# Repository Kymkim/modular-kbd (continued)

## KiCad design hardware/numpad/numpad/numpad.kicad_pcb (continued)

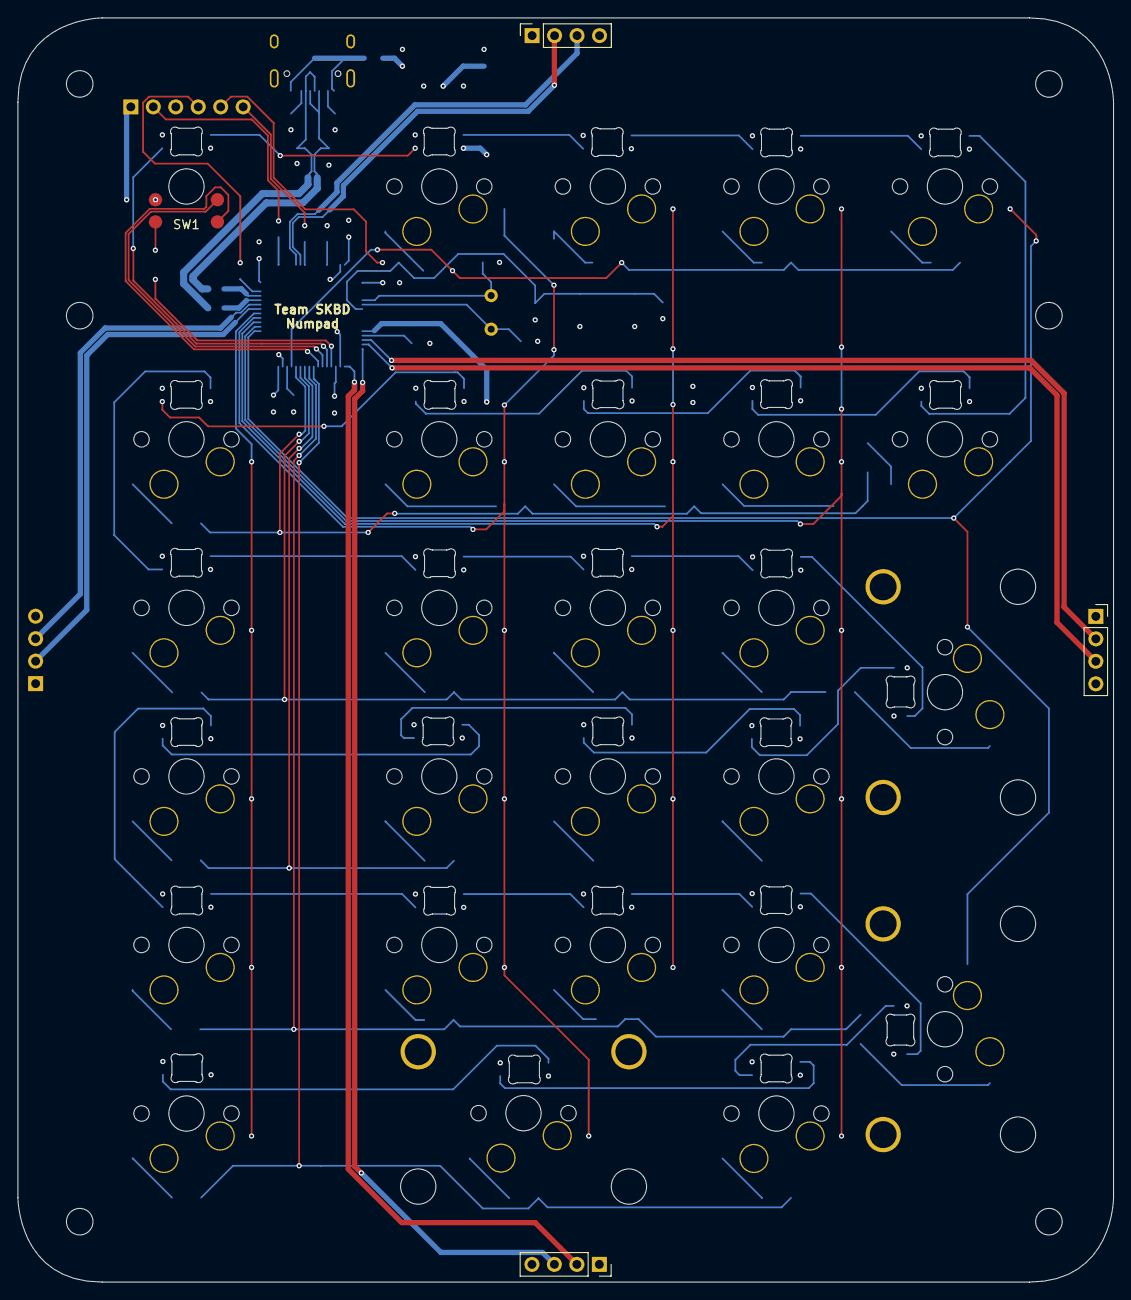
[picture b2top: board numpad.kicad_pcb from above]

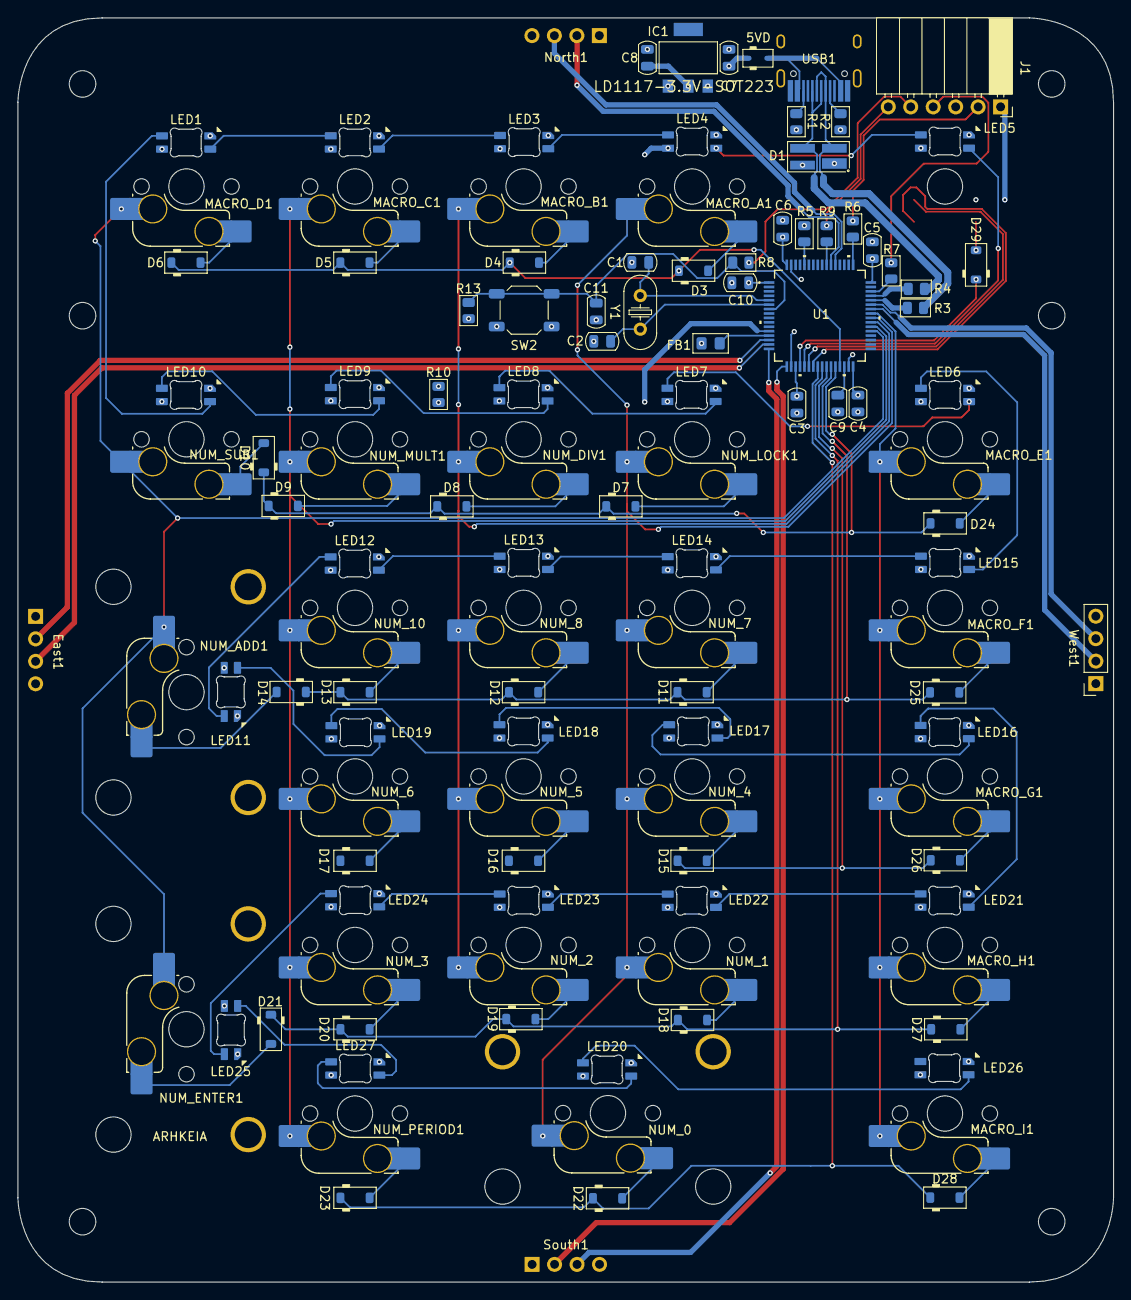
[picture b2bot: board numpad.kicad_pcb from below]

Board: 4 copper layers, 123.8 x 142.9 mm, 119 parts (112 on the bottom side), 100 nets.

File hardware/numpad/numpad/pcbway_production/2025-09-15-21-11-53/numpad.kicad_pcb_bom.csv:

Designator,Quantity,Value,Footprint,Package,MPN,DNP,Mount_Type,Description,Specifications,Manufacturer
"C1, C2",2,20pF,C_0805_2012Metric,,,,smt,"SMD 0805 MLCC capacitor, Alternate KiCad Library",,
"C10, C7",2,1uF,C_0805_2012Metric,,,,smt,"SMD 0805 MLCC capacitor, Alternate KiCad Library",,
C11,1,0.1uF,C_0805_2012Metric,,,,smt,"SMD 0805 MLCC capacitor, Alternate KiCad Library",,
"C3, C4, C5, C6",4,100nF,C_0805_2012Metric,,,,smt,"SMD 0805 MLCC capacitor, Alternate KiCad Library",,
C8,1,10uF,C_0805_2012Metric,,,,smt,"SMD 0805 MLCC capacitor, Alternate KiCad Library",,
C9,1,4.7uF,C_0805_2012Metric,,,,smt,"SMD 0805 MLCC capacitor, Alternate KiCad Library",,
D1,1,PRTR5V0U2X,SOT-143_Handsoldering,,,,smt,"SOT-143 TVS Diode Array, 2 protected lines, 5.5V, Alternate KiCAD Library",,
"D10, D11, D12, D13, D14, D15, D16, D17, D18, D19, D20, D21, D22, D23, D24, D25, D26, D27, D28, D29, D3, D4, D5, D6, D7, D8, D9",27,1N4148W,D_SOD-123,,,,smt,"SOD-123 Diode, Small Signal, Fast Switching, 75V, 150mA, 4ns, Alternate KiCad Library",,
D2,1,BAT60JFILM,D_SOD-323,,,,smt,Diode,,
"EAST, NORTH, SOUTH, WEST",4,Conn_01x04,PinSocket_1x04_P2.54mm_Vertical,,1-0401FBV0T,,tht,HEADER 1x4 MALE PINS 0.100” 180deg,HEADER 1x4 MALE PINS 0.100” 180deg,TAD
FB1,1,Ferrite_Bead,Fuse_0805_2012Metric_Pad1.15x1.40mm_BigPads,,,,smt,"Ferrite bead, Alternate KiCAD Library",,
IC1,1,LD1117,SOT223,,LD1117S33CTR,,tht,"3.3V Voltage Regulator, SOT-223-3, Imax=0.8A, VinMax=15V, Vdrop=1V",,STMicroelectronics
J1,1,Conn_01x06,PinSocket_1x06_P2.54mm_Horizontal,,1-0601FBV0T,,tht,HEADER 1x6 MALE PINS 0.100” 180deg,HEADER 1x6 MALE PINS 0.100” 180deg,TAD
"LED1, LED10, LED11, LED12, LED13, LED14, LED15, LED16, LED17, LED18, LED19, LED2, LED20, LED21, LED22, LED23, LED24, LED25, LED26, LED27, LED3, LED4, LED5, LED6, LED7, LED8, LED9",27,MX_SK6812MINI-E,LED_MX_6028R,,,,smt,Reverse mount adressable LED (WS2812 protocol),,
"MACRO_A1, MACRO_B1, MACRO_C1, MACRO_D1, MACRO_E1, MACRO_F1, MACRO_G1, MACRO_H1, MACRO_I1, NUM_0, NUM_1, NUM_10, NUM_2, NUM_3, NUM_4, NUM_5, NUM_6, NUM_7, NUM_8, NUM_ADD1, NUM_DIV1, NUM_ENTER1, NUM_LOCK1, NUM_MULT1, NUM_PERIOD1, NUM_SUB1",26,MX_SW_HS,SW_MX_HS_CPG151101S11_1u,,,,smt,"Push button switch, normally open, two pins, 45° tilted, Kailh CPG151101S11 for Cherry MX style switches",,
"R1, R2",2,5.1k,R_0805_2012Metric,,,,smt,"SMD 0805 Chip Resistor, European Symbol, Alternate KiCad Library",,
R10,1,DNP,R_0805_2012Metric,,,Yes,smt,"SMD 0805 Chip Resistor, European Symbol, Alternate KiCad Library",,
R13,1,DNP,R_0805_2012Metric,,,Yes,smt,"SMD 0805 Chip Resistor, European Symbol, Alternate KiCad Library",,
"R3, R4, R6, R7, R8, R9",6,22,R_0805_2012Metric,,,,smt,"SMD 0805 Chip Resistor, European Symbol, Alternate KiCad Library",,
R5,1,10k,R_0805_2012Metric,,,,smt,"SMD 0805 Chip Resistor, European Symbol, Alternate KiCad Library",,
"S1, S2, S3",3,MX_stab,STAB_MX_P_2u,,,,tht,Cherry MX-style stabilizer,,
SW2,1,Push_Button,SW_SPST_SKQG_WithStem,,,,smt,Common 6mmx6mm Push Button,,
U1,1,~,LQFP64-10x10mm,,,,smt,,,
USB1,1,HRO-TYPE-C-31-M-12,HRO-TYPE-C-31-M-12-HandSoldering,,,,smt,,,
Y1,1,8MHz,Crystal_HC52-U_Vertical,,,,tht,8Mz Crystal,,

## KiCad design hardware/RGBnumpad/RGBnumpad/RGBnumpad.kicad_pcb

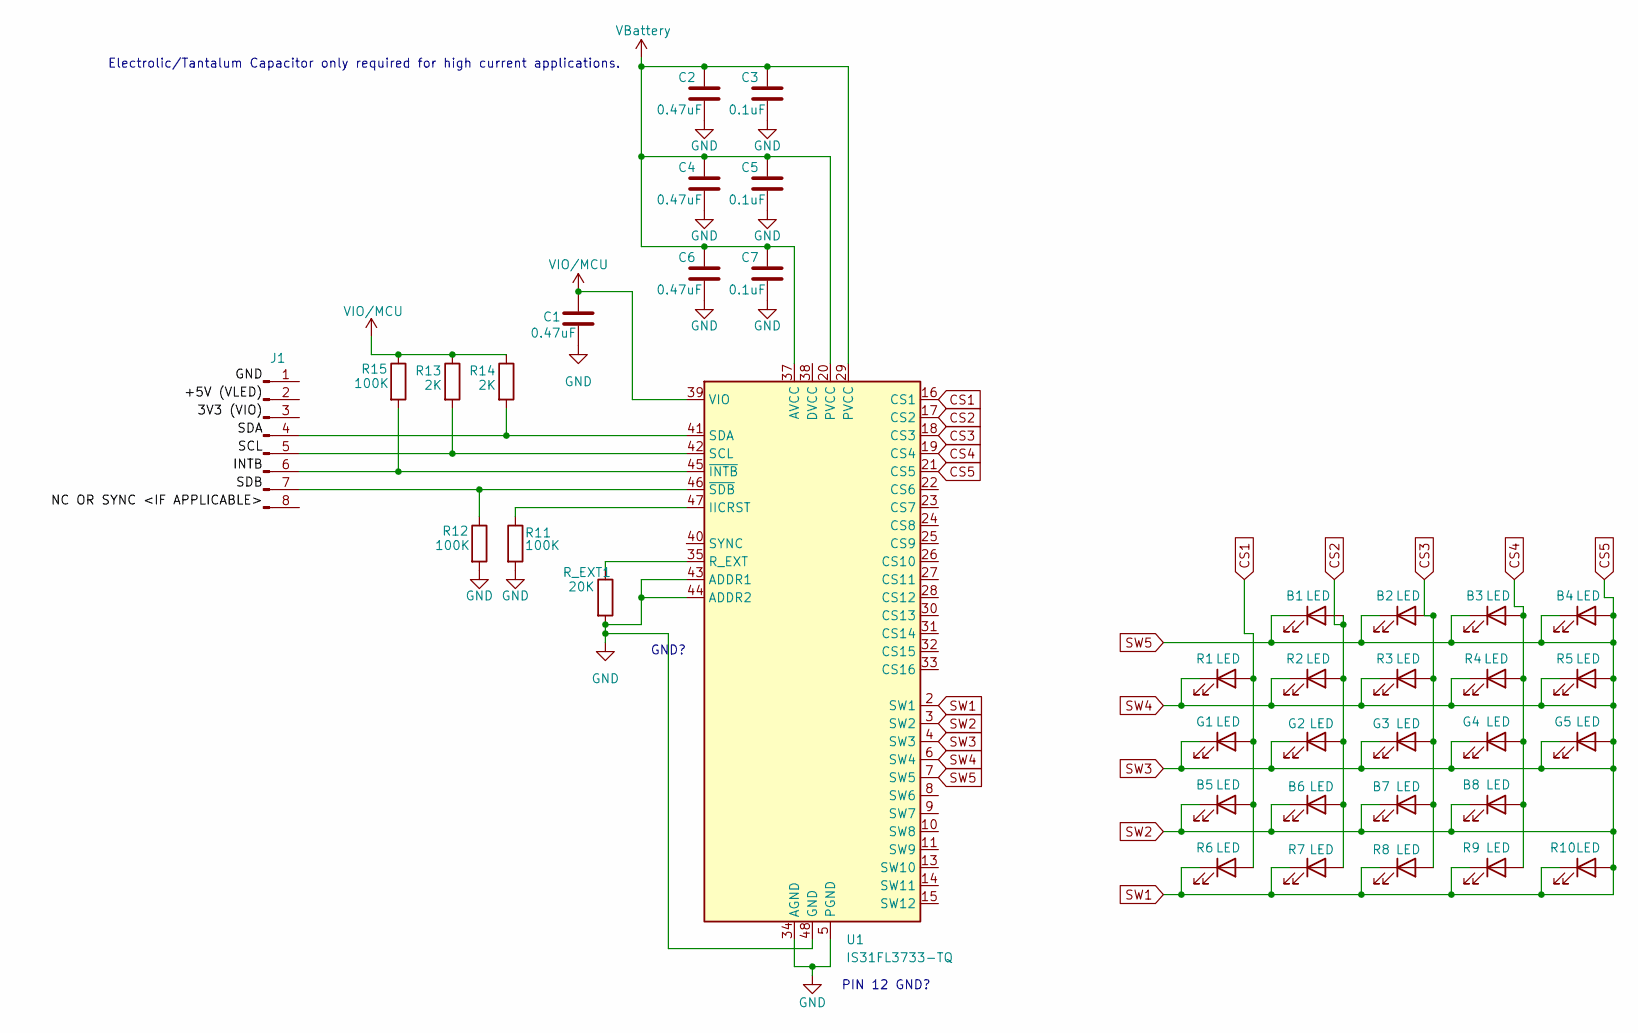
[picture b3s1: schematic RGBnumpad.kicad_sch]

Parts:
B1, B2, B3, B4, B5, B6, B7, B8: LED; LED_0805_2012Metric_Pad1.15x1.40mm_HandSolder
C1, C2, C4, C6: 0.47uF; C_0805_2012Metric_Pad1.18x1.45mm_HandSolder
C3, C5, C7: 0.1uF; C_0805_2012Metric_Pad1.18x1.45mm_HandSolder
G1, G2, G3, G4, G5: LED; LED_0805_2012Metric_Pad1.15x1.40mm_HandSolder
J1: (no value)
R1, R2, R3, R4, R5, R6, R7, R8, R9, R10: LED; LED_0805_2012Metric_Pad1.15x1.40mm_HandSolder
R11, R12, R15: 100K; R_0805_2012Metric_Pad1.20x1.40mm_HandSolder
R13, R14: 2K; R_0805_2012Metric_Pad1.20x1.40mm_HandSolder
R_EXT1: 20K; R_0805_2012Metric_Pad1.20x1.40mm_HandSolder
U1: IS31FL3733-TQ; TQFP-48-1EP_7x7mm_P0.5mm_EP5x5mm

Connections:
CS1: B5.2 (A), G1.2 (A), R1.2 (A), R6.2 (A), U1.16 (CS1)
CS2: B1.2 (A), B6.2 (A), G2.2 (A), R2.2 (A), R7.2 (A), U1.17 (CS2)
CS3: B2.2 (A), B7.2 (A), G3.2 (A), R3.2 (A), R8.2 (A), U1.18 (CS3)
CS4: B3.2 (A), B8.2 (A), G4.2 (A), R4.2 (A), R9.2 (A), U1.19 (CS4)
CS5: B1.1 (K), B2.1 (K), B3.1 (K), B4.1 (K), B4.2 (A), B5.1 (K), B6.1 (K), B7.1 (K), B8.1 (K), G1.1 (K), G2.1 (K), G3.1 (K), G4.1 (K), G5.1 (K), G5.2 (A), R1.1 (K), R2.1 (K), R3.1 (K), R4.1 (K), R5.1 (K), R5.2 (A), R6.1 (K), R7.1 (K), R8.1 (K), R9.1 (K), R10.1 (K), R10.2 (A), U1.2 (SW1), U1.3 (SW2), U1.4 (SW3), U1.6 (SW4), U1.7 (SW5), U1.21 (CS5)
GND: C1.2, C2.2, C3.2, C4.2, C5.2, C6.2, C7.2, R11.2, R12.2, R_EXT1.2, U1.5 (PGND), U1.12 (PGND), U1.34 (AGND), U1.43 (ADDR1), U1.44 (ADDR2), U1.48 (GND), U1.49 (GND)
unnamed: J1.4, R14.2, U1.41 (SDA)
unnamed: J1.5, R13.2, U1.42 (SCL)
unnamed: J1.6, R15.2, U1.45 (~INTB)
unnamed: J1.7, R12.1, U1.46 (~SDB)
unnamed: R11.1, U1.47 (IICRST)
unnamed: R_EXT1.1, U1.35 (R_EXT)
VBattery: C2.1, C3.1, C4.1, C5.1, C6.1, C7.1, U1.20 (PVCC), U1.29 (PVCC), U1.37 (AVCC)
VIO/MCU: C1.1, R13.1, R14.1, R15.1, U1.39 (VIO)

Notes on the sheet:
PIN 12 GND?
Electrolic/Tantalum Capacitor only required for high current applications.
GND?

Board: 2 copper layers, 37 parts (0 on the bottom side), 14 nets, no tracks yet.

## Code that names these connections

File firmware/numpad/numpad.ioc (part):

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Mcu.Name=STM32F446R(C-E)Tx
Mcu.Package=LQFP64
Mcu.UserName=STM32F446RETx
PA0-WKUP.Mode=Asynchronous
PA0-WKUP.Signal=UART4_TX
PA1.Mode=Asynchronous
PA1.Signal=UART4_RX
PA10.Mode=Asynchronous
PA10.Signal=USART1_RX
PA11.Mode=Device_Only
PA11.Signal=USB_OTG_FS_DM
PA12.Mode=Device_Only
PA12.Signal=USB_OTG_FS_DP
PA13.Mode=Serial_Wire
PA13.Signal=SYS_JTMS-SWDIO
PA14.Mode=Serial_Wire
PA14.Signal=SYS_JTCK-SWCLK
PA2.Mode=Asynchronous
PA2.Signal=USART2_TX
PA3.Mode=Asynchronous
PA3.Signal=USART2_RX
PA8.GPIOParameters=GPIO_Label
PA8.GPIO_Label=COL4
PA8.Signal=GPIO_Output
PA9.Mode=Asynchronous
PA9.Signal=USART1_TX
PB0.GPIOParameters=GPIO_PuPd,GPIO_Label
PB0.GPIO_Label=ROW4
PB0.GPIO_PuPd=GPIO_PULLDOWN
PB0.Signal=GPIO_Input
PB1.GPIOParameters=GPIO_PuPd,GPIO_Label
PB1.GPIO_Label=ROW3
PB1.GPIO_PuPd=GPIO_PULLDOWN
PB1.Signal=GPIO_Input
PB10.GPIOParameters=GPIO_PuPd,GPIO_Label
PB10.GPIO_Label=ROW1SR
PB10.GPIO_PuPd=GPIO_PULLDOWN
PB10.Signal=GPIO_Input
PB2.GPIOParameters=GPIO_PuPd,GPIO_Label
PB2.GPIO_Label=ROW2
PB2.GPIO_PuPd=GPIO_PULLDOWN
PB2.Signal=GPIO_Input
PB4.GPIOParameters=GPIO_Label
PB4.GPIO_Label=WDebug
PB4.Signal=GPIO_Output
PB5.GPIOParameters=GPIO_Label
PB5.GPIO_Label=SDebug
PB5.Signal=GPIO_Output
PB6.GPIOParameters=GPIO_Label
PB6.GPIO_Label=EDebug
PB6.Signal=GPIO_Output
PB7.GPIOParameters=GPIO_Label
PB7.GPIO_Label=NDebug
PB7.Signal=GPIO_Output
PB8.Mode=I2C
PB8.Signal=I2C1_SCL
PB9.Mode=I2C
PB9.Signal=I2C1_SDA
PC12.Mode=Asynchronous
PC12.Signal=UART5_TX
PC4.GPIOParameters=GPIO_PuPd,GPIO_Label
PC4.GPIO_Label=ROW6
PC4.GPIO_PuPd=GPIO_PULLDOWN
PC4.Signal=GPIO_Input
PC5.GPIOParameters=GPIO_PuPd,GPIO_Label
PC5.GPIO_Label=ROW5
PC5.GPIO_PuPd=GPIO_PULLDOWN
PC5.Signal=GPIO_Input
PC7.GPIOParameters=GPIO_Label
PC7.GPIO_Label=COL1
PC7.Signal=GPIO_Output
PC8.GPIOParameters=GPIO_Label
PC8.GPIO_Label=COL2
PC8.Signal=GPIO_Output
PC9.GPIOParameters=GPIO_Label
PC9.GPIO_Label=COL3
PC9.Signal=GPIO_Output
PD2.Mode=Asynchronous
PD2.Signal=UART5_RX
PH0-OSC_IN.Mode=HSE-External-Oscillator
PH0-OSC_IN.Signal=RCC_OSC_IN
PH1-OSC_OUT.Mode=HSE-External-Oscillator
PH1-OSC_OUT.Signal=RCC_OSC_OUT
board=custom

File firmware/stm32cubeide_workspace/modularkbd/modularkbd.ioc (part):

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Mcu.Name=STM32F446R(C-E)Tx
Mcu.Package=LQFP64
Mcu.UserName=STM32F446RETx
PA0-WKUP.Mode=Asynchronous
PA0-WKUP.Signal=UART4_TX
PA1.Mode=Asynchronous
PA1.Signal=UART4_RX
PA10.Mode=Asynchronous
PA10.Signal=USART1_RX
PA11.Mode=Device_Only
PA11.Signal=USB_OTG_FS_DM
PA12.Mode=Device_Only
PA12.Signal=USB_OTG_FS_DP
PA13.Mode=JTAG_5_pins
PA13.Signal=SYS_JTMS-SWDIO
PA14.Mode=JTAG_5_pins
PA14.Signal=SYS_JTCK-SWCLK
PA15.Mode=JTAG_5_pins
PA15.Signal=SYS_JTDI
PA2.Mode=Asynchronous
PA2.Signal=USART2_TX
PA3.Mode=Asynchronous
PA3.Signal=USART2_RX
PA5.Signal=S_TIM2_CH1_ETR
PA6.Signal=S_TIM3_CH1
PA7.Signal=S_TIM3_CH2
PA8.Signal=GPIO_Output
PA9.Mode=Asynchronous
PA9.Signal=USART1_TX
PB0.Signal=GPIO_Input
PB1.Signal=GPIO_Input
PB10.Signal=GPIO_Input
PB2.Signal=GPIO_Input
PB3.Mode=JTAG_5_pins
PB3.Signal=SYS_JTDO-SWO
PB4.Mode=JTAG_5_pins
PB4.Signal=SYS_JTRST
PB6.Mode=I2C
PB6.Signal=I2C1_SCL
PB7.Mode=I2C
PB7.Signal=I2C1_SDA
PC10.Mode=Asynchronous
PC10.Signal=USART3_TX
PC11.Mode=Asynchronous
PC11.Signal=USART3_RX
PC12.Mode=Asynchronous
PC12.Signal=UART5_TX
PC4.Signal=GPIO_Input
PC5.Signal=GPIO_Input
PC6.Signal=GPIO_Output
PC7.Signal=GPIO_Output
PC8.Signal=GPIO_Output
PC9.Signal=GPIO_Output
PD2.Mode=Asynchronous
PD2.Signal=UART5_RX
PH0-OSC_IN.Mode=HSE-External-Oscillator
PH0-OSC_IN.Signal=RCC_OSC_IN
PH1-OSC_OUT.Mode=HSE-External-Oscillator
PH1-OSC_OUT.Signal=RCC_OSC_OUT
RCC.HSE_VALUE=8000000
board=custom

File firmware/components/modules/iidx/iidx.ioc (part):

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Mcu.Name=STM32F446R(C-E)Tx
Mcu.Package=LQFP64
Mcu.UserName=STM32F446RETx
PA0-WKUP.GPIOParameters=GPIO_Label
PA0-WKUP.GPIO_Label=SCRATCH A
PA0-WKUP.Signal=S_TIM2_CH1_ETR
PA1.GPIOParameters=GPIO_Label
PA1.GPIO_Label=SCRATCH B
PA1.Signal=S_TIM2_CH2
PA10.GPIOParameters=GPIO_Label
PA10.GPIO_Label=COL 1
PA10.Signal=GPIO_Output
PA11.Mode=Device_Only
PA11.Signal=USB_OTG_FS_DM
PA12.Mode=Device_Only
PA12.Signal=USB_OTG_FS_DP
PA13.GPIOParameters=GPIO_Label
PA13.GPIO_Label=TMS
PA13.Mode=Serial_Wire
PA13.Signal=SYS_JTMS-SWDIO
PA14.GPIOParameters=GPIO_Label
PA14.GPIO_Label=TCK
PA14.Mode=Serial_Wire
PA14.Signal=SYS_JTCK-SWCLK
PA2.GPIOParameters=GPIO_Label
PA2.GPIO_Label=USART_TX
PA2.Mode=Asynchronous
PA2.Signal=USART2_TX
PA3.GPIOParameters=GPIO_Label
PA3.GPIO_Label=USART_RX
PA3.Mode=Asynchronous
PA3.Signal=USART2_RX
PA5.GPIOParameters=GPIO_Label
PA5.GPIO_Label=LD2 [Green Led]
PA5.Signal=GPIO_Output
PA6.GPIOParameters=GPIO_Label
PA6.GPIO_Label=LEFT LASER A
PA6.Signal=S_TIM3_CH1
PA7.GPIOParameters=GPIO_Label
PA7.GPIO_Label=LEFT LASER B
PA7.Signal=S_TIM3_CH2
PA8.GPIOParameters=GPIO_Label
PA8.GPIO_Label=COL 3
PA8.Signal=GPIO_Output
PA9.GPIOParameters=GPIO_Label
PA9.GPIO_Label=COL 2
PA9.Signal=GPIO_Output
PB12.GPIOParameters=GPIO_Label
PB12.GPIO_Label=EFFECT
PB12.Signal=GPIO_Input
PB13.GPIOParameters=GPIO_Label
PB13.GPIO_Label=VEFX
PB13.Signal=GPIO_Input
PB14.GPIOParameters=GPIO_PuPd,GPIO_Label
PB14.GPIO_Label=SEL
PB14.GPIO_PuPd=GPIO_PULLDOWN
PB14.Signal=GPIO_Input
PB15.GPIOParameters=GPIO_PuPd,GPIO_Label
PB15.GPIO_Label=START
PB15.GPIO_PuPd=GPIO_PULLDOWN
PB15.Signal=GPIO_Input
PB6.GPIOParameters=GPIO_Label
PB6.GPIO_Label=RIGHT LASER B
PB6.Signal=S_TIM4_CH1
PB7.GPIOParameters=GPIO_Label
PB7.GPIO_Label=RIGHT LASER A
PB7.Signal=S_TIM4_CH2
PB8.Mode=CAN_Activate
PB8.Signal=CAN1_RX
PB9.Mode=CAN_Activate
PB9.Signal=CAN1_TX
PC13.GPIOParameters=GPIO_Label,GPIO_ModeDefaultEXTI
PC13.GPIO_Label=B1 [Blue PushButton]
PC13.GPIO_ModeDefaultEXTI=GPIO_MODE_IT_FALLING
PC13.Signal=GPXTI13
PC14-OSC32_IN.Mode=LSE-External-Oscillator
PC14-OSC32_IN.Signal=RCC_OSC32_IN
PC15-OSC32_OUT.Mode=LSE-External-Oscillator
PC15-OSC32_OUT.Signal=RCC_OSC32_OUT
PC6.GPIOParameters=GPIO_PuPd,GPIO_Label
PC6.GPIO_Label=KEY 1
PC6.GPIO_PuPd=GPIO_PULLDOWN
PC6.Signal=GPXTI6
PC7.GPIOParameters=GPIO_Label
PC7.GPIO_Label=ROW 3
PC7.Signal=GPIO_Input
PC8.GPIOParameters=GPIO_Label
PC8.GPIO_Label=ROW 2
PC8.Signal=GPIO_Input
PC9.GPIOParameters=GPIO_Label
PC9.GPIO_Label=ROW 1
PC9.Signal=GPIO_Input
PH0-OSC_IN.Mode=HSE-External-Oscillator
PH0-OSC_IN.Signal=RCC_OSC_IN
PH1-OSC_OUT.Mode=HSE-External-Oscillator
PH1-OSC_OUT.Signal=RCC_OSC_OUT
RCC.HSE_VALUE=8000000
RCC.SYSCLKFreq_VALUE=72000000
RCC.SYSCLKSource=RCC_SYSCLKSOURCE_PLLCLK
board=NUCLEO-F446RE
boardIOC=true

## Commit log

2025-03-08 initial commit (i think)
2025-03-19 mainboard stuff
2025-03-21 updated code (untested)
2025-03-24 config update
2025-03-24 started on test module
2025-03-24 test module stuff
2025-06-06 config for the can bus for module
2025-06-07 CAN main start
2025-06-10 add git branch for can
2025-06-11 file restructuring and minor code edits with config
2025-06-11 deleted unused files
2025-06-13 update USB product string and include paths for CAN module. starting code with CAN as loopback to check if its working. not yet tested
2025-06-19 peepee
2025-06-19 Add working 2x2 matrix keypad main.c
2025-06-19 Add full STM32CubeIDE SKBD_Matrix project for 2x2 keypad
2025-06-20 Add USB device descriptor and configuration for KMDVX Controller
    - Implemented USB device descriptors in usbd_desc.c for HID functionality.
    - Created iidx.ioc file for STM32CubeMX configuration, defining peripherals and settings.
    - Added platformio.ini for PlatformIO project configuration targeting Nucleo-F446RE.
    - Introduced stm32pio.ini for integration with STM32CubeMX and PlatformIO commands.
2025-06-22 minor code change
2025-06-22 not working. should make the led flash if button on pa10 is pressed.
2025-06-24 Note on STM32 CAN Filter Bank Number
2025-06-25 working transmit data
2025-06-25 fix: update CAN filter bank configuration to valid range
2025-06-25 can finally works
2025-06-25 Add CAN communication and GPIO control functionality
    - Created HAL configuration file for STM32F1xx (stm32f1xx_hal_conf.h).
    - Added interrupt handler definitions in stm32f1xx_it.h.
    - Implemented CAN initialization and configuration in can.c.
    - Configured GPIO pins for output and external interrupts in gpio.c.
    - Developed main application logic in main.c for toggling an LED and sending CAN messages.
    - Implemented MSP initialization and de-initialization for CAN in stm32f1xx_hal_msp.c.
2025-06-25 Initial folder structure. added read me. will explain more details later
2025-06-26 some readme changes
2025-06-26 explaination for the mainboard stuff
2025-06-26 initial main board
2025-07-01 nkro support :)
2025-07-01 4key miku keyboard with nkro
2025-07-02 initial stuff for recieving from can
2025-07-02 separated usb code to the library. will add 6key rollover support later :)
2025-07-03 6 Key Rollover Code Comments
    check the addHIDReport function and the main function, memset line, verify
2025-07-03 separated HID struct for both nkro and 6kro
2025-07-12 Initial branch for can tester for the mainboard
2025-07-15 sample 2x2 modul
2025-07-15 folder re-structuring
2025-07-15 file restructure
2025-07-15 prototype mainboard done!
2025-07-22 dynamic mode implementation
2025-08-18 mergy
2025-08-18 Licensce and file restructuring. Housekeeping rules
2025-08-18 update read me
2025-08-18 connectors for other modules
2025-08-18 Numpad IOC
2025-08-19 Create LICENSE
2025-08-20 numpad ioc update for future compability with sync uart
2025-08-20 initial code for numpadtesting with UART
2025-08-22 DMA Queue implemntation using UART
2025-08-24 revised DMA Queue
2025-08-25 documentation and inactive mode code
2025-08-25 fixed compiler errors
2025-08-25 added todo tasks
2025-08-25 typo fix
2025-08-25 tpyo fix
2025-08-25 USB; Coupling Caps; and XTAL schematic
2025-08-26 Some work on the GPIO, enabled DMA for TX as well
2025-08-26 numpad, connections, and more
2025-08-27 progreers
2025-08-27 stuff
2025-08-27 draft pcb
2025-08-28 typo in schematic
    i changed the GNDA to AGND
2025-08-28 diode name + agnd --> gnd
    added the bat and added the jump from agnd and gnd that mayyyyy be needed
2025-09-01 RGBnumpad
    Added RBGnumpad w/ symbols
    Still need to assign footprints
2025-09-02 RGBnumpad Footprint
    SMD 0805 hand solder footprints assigned to all of the parts on schematic
2025-09-02 ICANTDOTHISRGBPCB
    ICANTDOITICANTDOITICANTDOITICANTDOITICANTDOITICANTDOITICANTDOITICANTDOITICANTDOITICANTDOITICANTDOITICANTDOITICANTDOITICANTDOITICANTDOITICANTDOITICANTDOITICANTDOITICANTDOITICANTDOIT
2025-09-02 some config changes
2025-09-03 rgb matrix and drc rules
2025-09-03 comments
2025-09-03 fixed grid
    19.05 is grid size for pcb editor
2025-09-04 backup
2025-09-04 ROT_SW
    Disconnect after S diode, ROT_SW
2025-09-04 LEDs attached to switches
    LEDs are assigned to the switches now
2025-09-05 some fixy
2025-09-05 sotfware fore re-enum and clock stabilize delay
2025-09-07 6kro rollback
2025-09-07 remaking a new firmware
2025-09-07 working 6kro
2025-09-08 archived old files
2025-09-08 Update Main for 2x2 HID keyboard
    Updated the main.c file to implement a 2x2 matrix keyboard functionality. The code now reads key presses and sends corresponding HID reports.
2025-09-09 pcb stuff
2025-09-09 diodes placed except top 2 rows
    🐷
2025-09-09 LEDs
    Placed all LEDs
2025-09-10 pcb design draft
2025-09-11 bom list and some minor changes
2025-09-11 messages
2025-09-14 commit before merging to dev
2025-09-14 docs change
2025-09-14 readmeupdate
2025-09-16 really necessary silkscreen on pcb numpad
2025-09-17 removed a file
2025-09-17 amogus sussy burger
2025-09-21 idk actually
2025-09-22 UART STUFF
2025-09-22 initial 65 perc
2025-09-23 keyboardMatrix
    finished the kbd matrix layout. subject to review. <3
2025-09-23 uart dma stuff
2025-09-23 numpad configuration
2025-09-23 removed buggy file
2025-09-24 PCB start for keyboard
2025-09-24 more pcb work
2025-09-24 keyboard updates
2025-09-24 chicken butt
2025-09-24 keyboard
2025-09-25 dma sending stuff thru uart
2025-09-25 stuff stabs O
2025-09-25 switches
2025-09-27 layout adjustment
2025-09-29 handshake event implementation
2025-09-29 somebody once told me the world is gonna roll me
2025-10-07 LEDs
2025-10-07 prototypeNumpadCase
    not done yet. only bottom done need extrude cuts on the top for mx holes
2025-10-13 completed protype numpad case
    fuck my chungus life
2025-10-13 stl files for numpad
    to da 3-d printer
2025-10-22 safty
2025-10-24 footprint
2025-10-28 diode placement
2025-10-29 pushy
2025-10-31 traces
2025-11-04 Traces
    67676767676767
    SIX SEVEN
2025-11-05 traces
    676767676767
2025-11-05 traces
    six seven
2025-11-07 autoroute
2025-11-08 fixed grouped words
    madafakers
2025-11-09 pcb update
2025-11-11 quotes
2025-11-11 minor stuff
2025-11-11 67 prototype
2025-11-12 somewhat works
2025-11-12 clean up
2025-11-12 ntearsntei
2025-11-17 googoogaagaa babies
2025-11-19 Implement encoder processing for keypress updates
    Added encoder processing to handle rotary input and update keypress reports accordingly.
2025-11-19 top mxPlate half
    not done yet but the top thing is done without the back part
2025-11-20 fnished top plate
    heeheehawhaw
2025-11-20 PhoPlate/Secure
    plate and supporting beams based on nolan keeb design
2025-11-21 left side PhoBottomCase complete
    i finished the left side of the bottom of the case. may need more joint in middle and need screw holes
2025-11-22 PhoBottomRight Case + Assembly
    Both have been completed. awaiting m3 holes and top plate.
2025-11-22 assets
2025-11-22 reorg
2025-11-23 fixed alignment with wireframe
    need top alignment with screws and etch and rubber feet
2025-11-24 COMPLETED CASE
    pending engrave and writing
2025-11-25 print bottom
    hehehehaw
2025-11-26 67 partial code
2025-11-26 Updated key matrix
2025-11-27 complete Numpad Case
    gasket mounted goodness
2025-12-02 FINISHED FUCKING CASES
    RAHHHHHHHHHHHHHHHHH
2025-12-03 SQUIRT
2025-12-08 Refactor main.c for improved functionality and structure
    Updated the main.c file to include additional functionalities and improved code structure. Adjusted key mappings and enhanced UART message handling.
2025-12-08 Modify GPIO initialization for additional pins
    Updated GPIO configuration to include additional pins.
2025-12-10 thingy!
2025-12-10 stuff
    STL
